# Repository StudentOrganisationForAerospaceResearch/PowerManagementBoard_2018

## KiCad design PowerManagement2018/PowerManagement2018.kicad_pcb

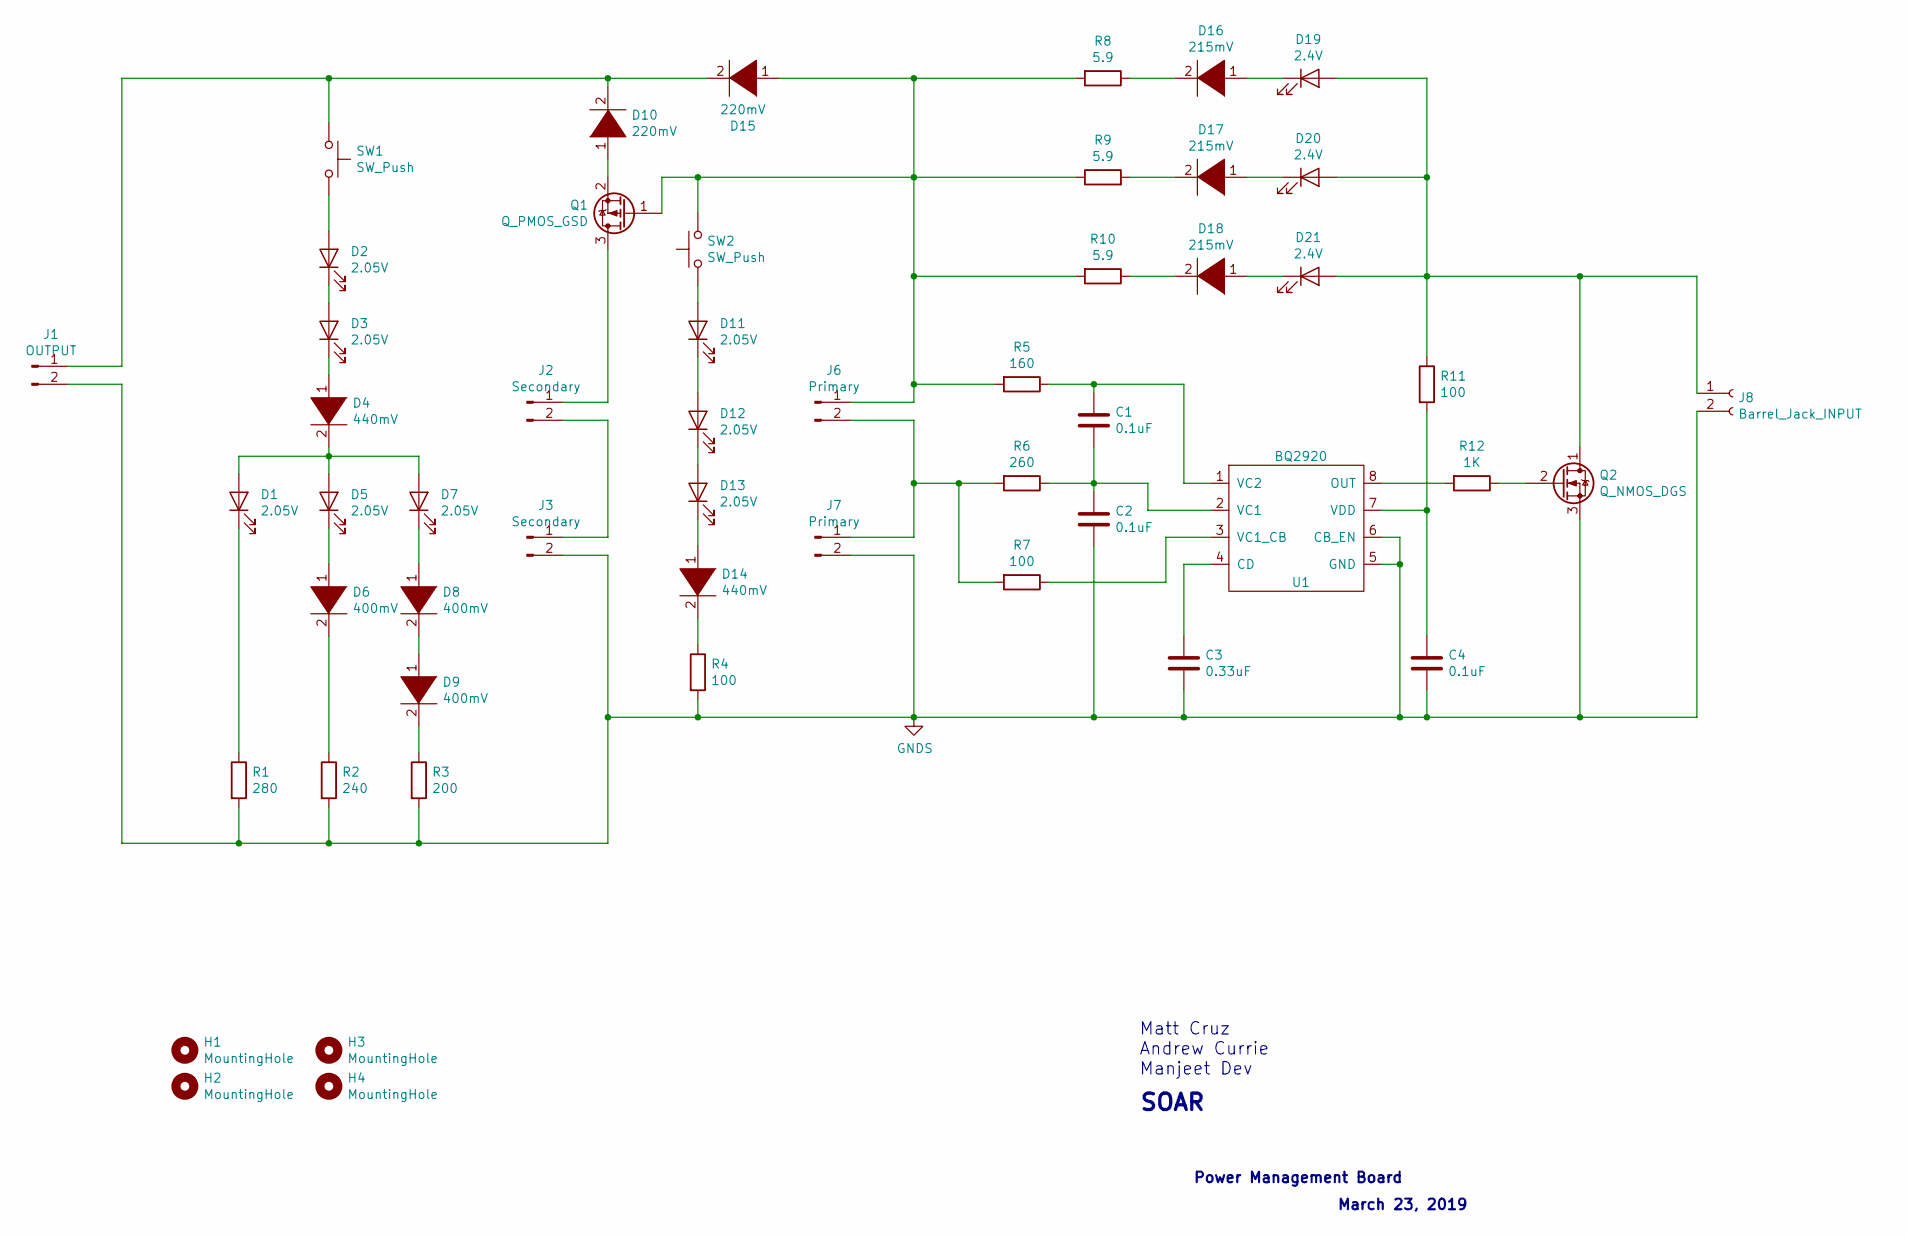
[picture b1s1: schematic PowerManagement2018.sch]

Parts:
C1, C2, C4: 0.1uF; CL05B104KP5NNNC (0.1uF)
C3: 0.33uF; CL21B334KBFNNNE (0.33uF)
D1, D5, D7: 2.05V; SML-D12U1WT86 (2.05V 10mA)
D2, D3, D11, D12, D13: 2.05V; LTST-C190KFKT (2.05V 30mA)
D4, D14: 440mV; BAT42WS-7-F (0.44V 30mA)
D6, D8, D9: 400mV; BAT46W-E3-08(0.4V10mA)
D10, D15: 220mV; UPS115U (Diode 0.22V)
D16, D17, D18: 215mV; PMEG1020EH (215mV diode)
D19, D20, D21: 2.4V; XZMYH160S (2.5V LED)
H1, H2, H3, H4: MountingHole; MountingHole_3mm
J1: OUTPUT; Molex_Micro-Fit_3.0_43045-0400_2x02_P3.00mm_Horizontal
J2, J3: Secondary; deans connector
J6, J7: Primary; deans connector
J8: Barrel_Jack_INPUT; CUI_PJ-102A_2.5mm_DC_JACK
Q1: Q_PMOS_GSD; MCH3383(PMOS;0.8Vth)
Q2: Q_NMOS_DGS; AO3414 (nmos)
R1: 280; RC0402(resistors)
R2: 240; RC0402(resistors)
R3: 200; RC0201(resistors)
R4, R7: 100; RC0201(resistors)
R5: 160; RC0402(resistors)
R6: 260; RC0402(resistors)
R8, R9, R10: 5.9; CRCW25125R90FKEGHP(5.9 ohms)
R11: 100; RT0603(resistors)
R12: 1K; RC0201(resistors)
SW1, SW2: SW_Push; 1301.9320 (button)
U1: BQ2920; bq29209

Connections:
GNDS: C2.2, C3.2, C4.2, J1.2, J3.2, J7.2, J8.2, Q2.3 (S), R1.2, R2.2, R3.2, R4.2, U1.5 (GND), U1.6 (CB_EN)
unnamed: C1.1, R5.1, U1.1 (VC2)
unnamed: C1.2, C2.1, R6.1, U1.2 (VC1)
unnamed: C3.1, U1.4 (CD)
unnamed: C4.1, R11.2, U1.7 (VDD)
unnamed: D1.1 (K), R1.1
unnamed: D1.2 (A), D4.2 (A), D5.2 (A), D7.2 (A)
unnamed: D2.1 (K), D3.2 (A)
unnamed: D2.2 (A), SW1.2
unnamed: D3.1 (K), D4.1 (K)
unnamed: D5.1 (K), D6.1 (K)
unnamed: D6.2 (A), R2.1
unnamed: D7.1 (K), D8.1 (K)
unnamed: D8.2 (A), D9.1 (K)
unnamed: D9.2 (A), R3.1
unnamed: D10.1 (K), Q1.2 (S)
unnamed: D10.2 (A), D15.2 (A), J1.1, SW1.1
unnamed: D11.1 (K), D12.2 (A)
unnamed: D11.2 (A), SW2.1
unnamed: D12.1 (K), D13.2 (A)
unnamed: D13.1 (K), D14.1 (K)
unnamed: D14.2 (A), R4.1
unnamed: D15.1 (K), J6.1, Q1.1 (G), R5.2, R8.2, R9.1, R10.2, SW2.2
unnamed: D16.1 (K), D19.1 (K)
unnamed: D16.2 (A), R8.1
unnamed: D17.1 (K), D20.1 (K)
unnamed: D17.2 (A), R9.2
unnamed: D18.1 (K), D21.1 (K)
unnamed: D18.2 (A), R10.1
unnamed: D19.2 (A), D20.2 (A), D21.2 (A), J8.1, Q2.1 (D), R11.1
unnamed: J2.1, Q1.3 (D)
unnamed: J2.2, J3.1
unnamed: J6.2, J7.1, R6.2, R7.2
unnamed: Q2.2 (G), R12.1
unnamed: R7.1, U1.3 (VC1_CB)
unnamed: R12.2, U1.8 (OUT)

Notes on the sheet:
Matt Cruz Andrew Currie Manjeet Dev
SOAR
Power Management Board
March 23, 2019

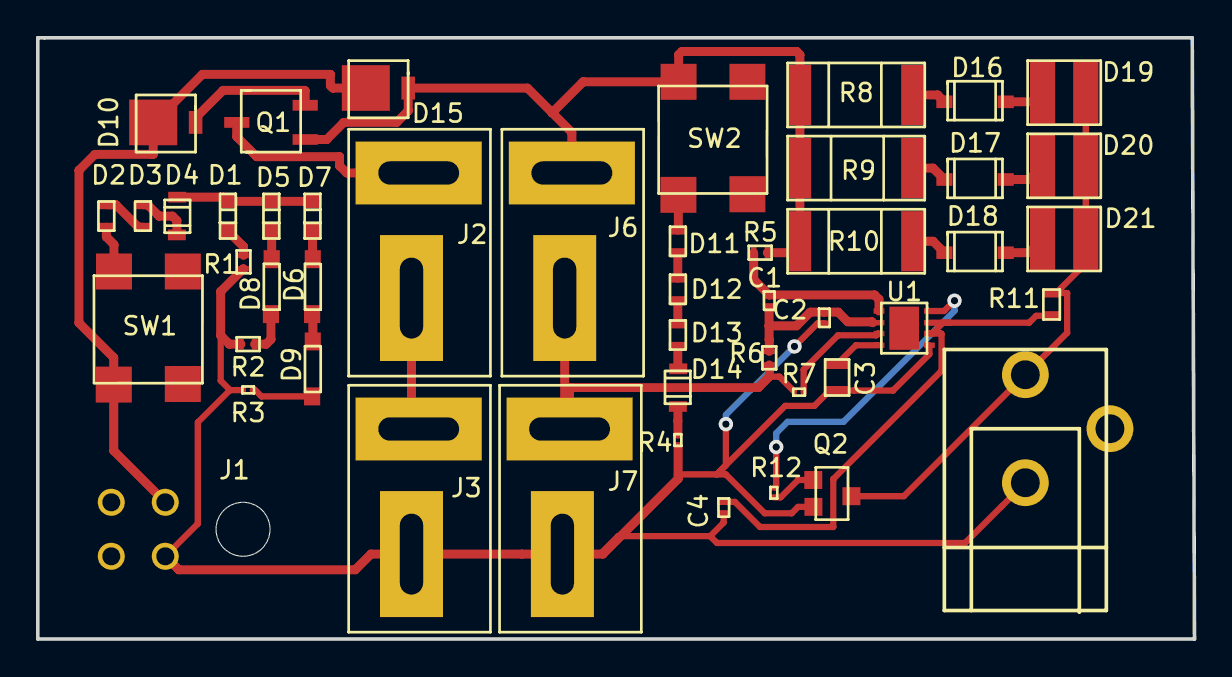
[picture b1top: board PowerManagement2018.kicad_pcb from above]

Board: 2 copper layers, 64.3 x 33.4 mm, 52 parts (0 on the bottom side), 36 nets.

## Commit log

2019-03-23 Combined system
    Battery charging system and battery switching system combined
